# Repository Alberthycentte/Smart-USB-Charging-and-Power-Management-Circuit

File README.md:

This custom-designed circuit board manages power distribution between a USB source, a rechargeable battery, and an external load. When connected to a USB power source, the circuit intelligently routes power to the load while charging the battery in parallel. Once the USB is disconnected, it seamlessly switches to battery power, ensuring uninterrupted operation of the connected device.

The design includes an onboard LED indicator that displays the charging status, making it easy to monitor battery activity at a glance. The compact layout and use of surface-mount components allow for efficient space utilization while maintaining clear signal routing and reliable performance.

Key Features

Automatic power path control between USB and battery

Simultaneous load powering and battery charging

Seamless switching to battery when USB is disconnected

LED indicator for real-time charging status

Compact and efficient PCB layout

Applications

This is deal for portable electronics, sensor modules, or any embedded system requiring a stable power supply with automatic source selection.

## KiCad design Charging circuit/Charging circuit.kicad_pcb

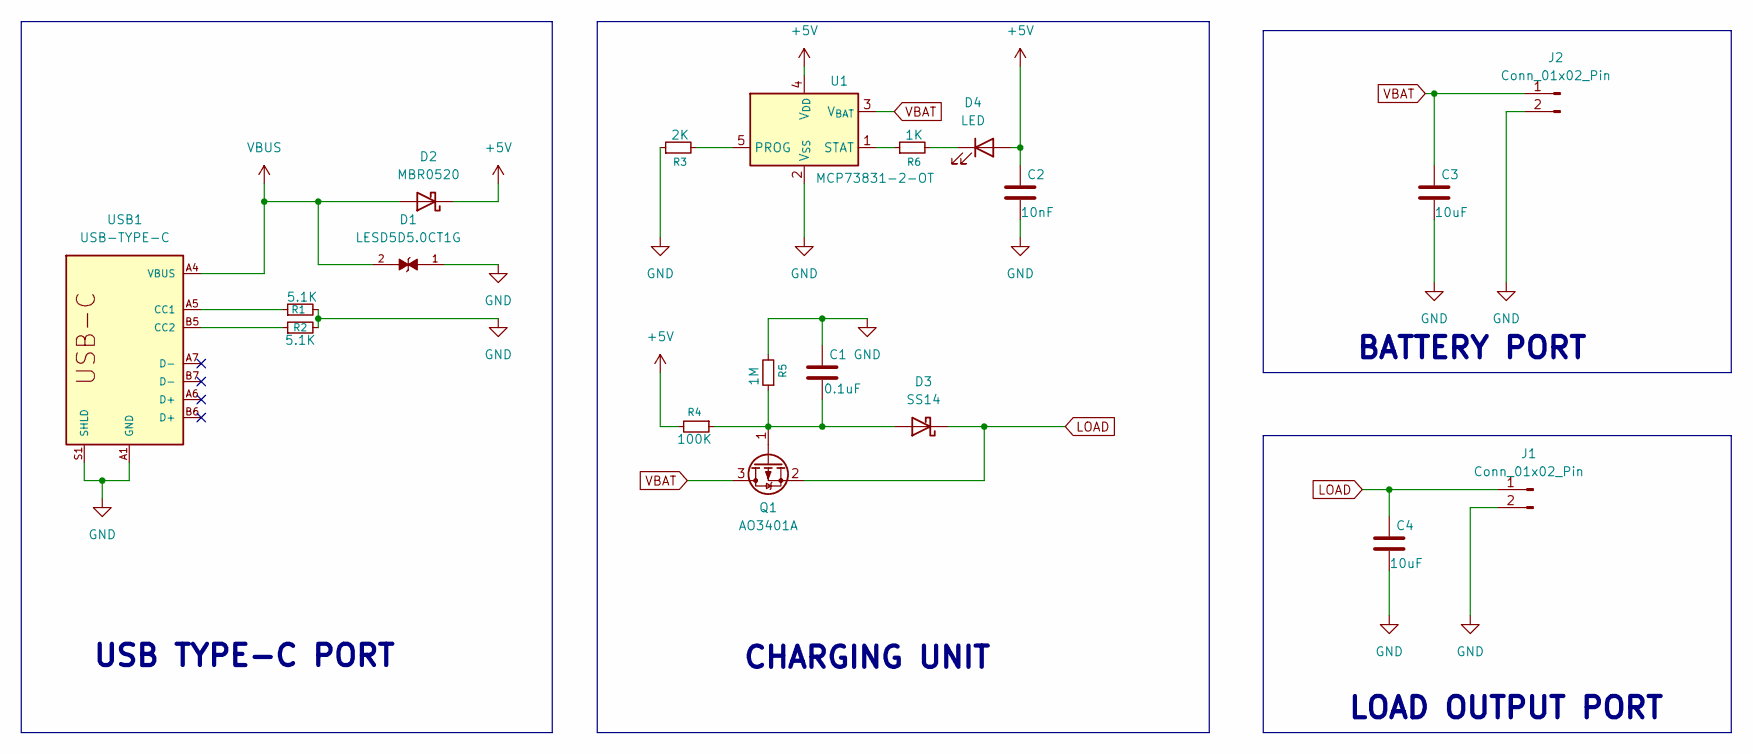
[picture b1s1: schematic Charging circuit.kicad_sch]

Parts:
C1: 0.1uF; C_0805_2012Metric
C2: 10nF; C_0805_2012Metric
C3, C4: 10uF; C_0805_2012Metric
D1: LESD5D5.0CT1G; TVS_LESD5D5.0CT1G; PARTREV O
D2: MBR0520; D_SOD-123
D3: SS14; D_SMA
D4: LED; LED_D3.0mm_Horizontal_O1.27mm_Z6.0mm
J1, J2: Conn_01x02_Pin; JST_PH_B2B-PH-K_1x02_P2.00mm_Vertical
Q1: AO3401A; SOT-23
R1, R2: 5.1K; R_0805_2012Metric
R3: 2K; R_0805_2012Metric
R4: 100K; R_Axial_DIN0204_L3.6mm_D1.6mm_P5.08mm_Horizontal
R5: 1M; R_Axial_DIN0204_L3.6mm_D1.6mm_P5.08mm_Horizontal
R6: 1K; R_0805_2012Metric
U1: MCP73831-2-OT; SOT-23-5
USB1: USB-TYPE-C; USBC.USB4110-GF-A

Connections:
+5V: C2.1, D2.1 (K), D4.2 (A), R4.2, U1.4 (V_{DD})
GND: C1.1, C2.2, C3.2, C4.2, D1.1, J1.2, J2.2, R1.2, R2.2, R3.1, R5.2, U1.2 (V_{SS}), USB1.A1 (GND), USB1.S1 (SHLD)
LOAD: C4.1, D3.1 (K), J1.1, Q1.2 (S)
unnamed: C1.2, D3.2 (A), Q1.1 (G), R4.1, R5.1
unnamed: D4.1 (K), R6.2
unnamed: R3.2, U1.5 (PROG)
unnamed: R6.1, U1.1 (STAT)
unnamed: R1.1, USB1.A5 (CC1)
unnamed: R2.1, USB1.B5 (CC2)
VBAT: C3.1, J2.1, Q1.3 (D), U1.3 (V_{BAT})
VBUS: D1.2, D2.2 (A), USB1.A4 (VBUS)

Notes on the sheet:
USB TYPE-C PORT
BATTERY PORT
LOAD OUTPUT PORT
CHARGING UNIT

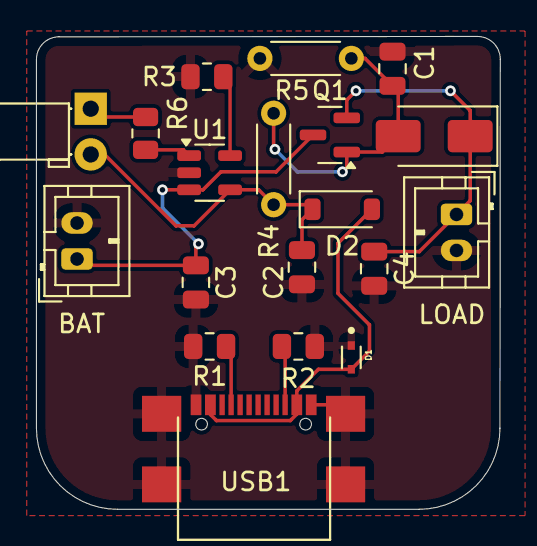
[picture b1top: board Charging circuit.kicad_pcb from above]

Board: 2 copper layers, 25.8 x 26.3 mm, 19 parts (0 on the bottom side), 11 nets.

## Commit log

2025-12-29 Enhance README with detailed circuit description
    Expanded the README to include detailed circuit functionality, key features, and applications.
2026-01-18 Rename simulation_image_top (4).png to simulation_image_top.png
2026-01-21 Rename simulation_image_bottom (4).png to simulation_image_bottom.png
2026-02-05 Fix typo in README description
